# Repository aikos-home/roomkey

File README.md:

# RoomKey

**A key for every room: a small touch screen on two mechanical keyboard switches, in a 64 × 64 mm
housing that plugs into a wall socket. Doorbell, intercom, alarm and lights, one press away.
Built on ESP32-C6, ESPHome and Home Assistant.**

[Deutsch](README.de.md)

> Status: pre-alpha prototype. The firmware runs on the touch board on the desk; the microphone is
> verified on hardware. The housing v0.4 and kit v0.12 are designed in CAD, not printed yet; printed and
> assembled so far are the front stack and chassis of kit v0.10. The hub PCB is designed, not manufactured.
> State of this page: 31 October 2026.

<p align="center">
  
  <br><em>Target design — an AI-generated concept render (Google Gemini), not a photo of a built device.</em>
</p>

<p align="center">
  
  <br><em>The current design in FreeCAD: housing v0.4 in a SCHUKO socket. Build files in <a href="hardware/">hardware/</a>.</em>
</p>

## What it is

- **Plugs into a wall socket.** It runs on 5 V from an unmodified, certified USB charger inside
  the housing: no mains wiring, no electrician. The room's normal light switch stays where it is.
- **A key with a screen.** A 1.47″ touch display on top of a mechanical keyboard switch.
  **Press** does the obvious thing, **hold** does the deliberate thing, and the screen always
  says which is which. Tap and swipe for the rest.
- **The doorbell in every bedroom.** It rings, shows who is calling, and you answer with the
  key: hold to talk, release to listen.
- **The alarm, where you are.** Armed at night? Hold the key for 1.5 s to disarm — Home
  Assistant decides whether that room is allowed to.
- **Local and standard.** ESPHome native API: Home Assistant discovers it with ordinary
  entities, events and actions. No cloud, no custom integration.

It is the in-house counterpart of [Klingelbox](https://github.com/aikos-home/intercom), the
open-hardware door intercom.

## Status

| Area | State |
|---|---|
| UI + interaction state machine (lights, alarm, doorbell, call, menu, info) | ✅ done — runs on the board, verified in simulator and on hardware (scripted tour) |
| Home Assistant contract (subscriptions, light.toggle, disarm script, events, actions) | ✅ **11/11 against a real Home Assistant** (2026.9 dev instance, `tools/ha_contract_test.py`): lights toggle, disarm via HA policy (NIGHT allowed, AWAY refused), ring → answer / talk / hang-up events; also 11/11 against the fake HA incl. audio (`tools/fake_home.py --test`) |
| Demo mode (everything works standalone, no HA needed) | ✅ on by default |
| Status LED (WS2812 on the PoC board; glow ring on the touch board) | ✅ implemented — colours per state, not visually checked |
| Microphone (INMP441) | ✅ **verified on hardware** — wired, recorded: 1 kHz test beep +30 dB, speech +18 dB over the room; 120 Hz high-pass removes knock/handling rumble. Test: `esphome/mic_test.yaml` + `tools/mic_check.py` |
| Intercom audio, voice v2 (shared `aikos_voice` block: RTP/L16 16 kHz, push-to-talk, call model) | ✅ **desk key on v2 since 02.10.**: aikos re-acceptance with the door 71/71; simulator on the same block (`tools/voice_host_check.py`). The key's own audio path (`roomkey.yaml`) stays as the fallback. Listening needs the speaker (WIP, below) |
| Speaker + ringtone (MAX98357A + Waveshare 2030 cavity speaker 8 Ω 2 W) | 🟡 **WIP / opt-in** — compiles, commented out; parts ordered |
| Touch variant of the board (tap / swipe) | 🟡 **WIP** — required by the target design; arrived 02.10.: display, tap and swipe work on the board (`esphome/roomkey_touch.yaml`); chat swipe in a real call, mic, amp and glow ring on it still untested |
| Intercom security | ✅ incoming audio accepted only during an active call; everything else is dropped unheard |
| Door station side | ⬜ other milestone — spec in [docs/intercom-protocol.md](docs/intercom-protocol.md) |
| Optional sensors: SHT31-D climate, LD2410C mmWave presence | 🟡 bought; climate on the shared I²C bus (no extra pins), radar on UART; both placed in the housing in CAD. Light sensor (VEML6030) only in the PCB build (decided 31.10.) |
| Housing (plug-in, 64 × 64) and kit, two electronics builds (hub PCB / self-wired) | 🟡 designed in CAD, 0 collisions ([hardware/](hardware/)); not printed in this revision. The visible front is to be cast in resin; hub PCB rev D for this housing designed (DRC 0), not ordered |

## Inputs

| Screen | Tap | Swipe ↑ | Swipe ↓ | Key press | Key hold |
|---|---|---|---|---|---|
| Home | wakes, shows a hint — never an action | menu | — | all lights | menu · **disarm** when armed |
| Ringing | answer | — | silence this room | answer (on key-down) | answer + talk |
| Call | hold the disc = talk | — | hang up | hang up | push-to-talk |
| Menu | select | — | close | next | select |
| Alarm | — | — | — | hint | **disarm** (1.5 s) |

* A tap never switches anything on the home screen: fingers brush the screen whenever they
  press the key.
* A mechanical press always starts as a touch; key-down cancels that touch, so one press never
  fires twice.
* The key works on a dark screen — slap it in the dark to switch the lights.

## Hardware

The desk prototype runs on a **Waveshare ESP32-C6-LCD-1.47** (no touch). The target is the
**ESP32-C6-Touch-LCD-1.47** — same chip, touch layer, different size and pinout; the firmware
switches with one line.

### Board comparison (Waveshare drawings)

| | ESP32-C6-LCD-1.47 (PoC, non-touch) | ESP32-C6-Touch-LCD-1.47 |
|---|---|---|
| Outline | 36.4 × 20.3 mm bare PCB | 44.5 × 24.6 mm in black frame, 10.6 mm thick |
| Header | 2 × 9, one GND | 2 × 11, two GND, VBUS, VBAT |
| Mic SCK/WS/SD, L/R | IO18/IO19/IO23, L/R→IO0 | IO7/IO8/IO17, L/R→GND or IO3 |
| Amp BCLK/LRC/DIN, power | IO18/IO19/IO20, 5V | IO7/IO8/IO16, VBUS |
| Key | **IO1** + **IO2** (or the BOOT button) | BOOT + GND |

Firmware: swap the `board:` line in `roomkey.yaml`. The keycap is **not** interchangeable.

### Wiring (desk prototype: ESP32-C6-LCD-1.47)

| Part | Pins |
|---|---|
| Mechanical key switch | **IO1** + **IO2** (IO2 is held LOW by the firmware, because the header's only GND feeds the mic; no soldering; the onboard BOOT button works as the key too) |
| INMP441 mic | VDD→**3V3**, GND→**GND**, L/R→**IO0** (held low by firmware — the header has only one GND), SCK→**IO18**, WS→**IO19**, SD→**IO23** |
| I²S amp (WIP, e.g. MAX98357A) | VIN→**5V**, GND, BCLK→**IO18**, LRC→**IO19**, DIN→**IO20** |

INMP441 is bottom-port: the hole in its PCB must face the room. Mic and amp share the I²S
clocks → half-duplex by design (= push-to-talk, no echo).

Speaker: Waveshare 2030 cavity speaker (8 Ω, 2 W, 20 × 30 × 5.5 mm). Standing on its edge it fits
behind a side wing of the 55 × 55 mm plate — see the [fit check](docs/fit-check-speaker.png).

The housing, both electronics builds, print files and the build guide are in [hardware/](hardware/).

## Quick start

```bash
cd esphome
esphome run roomkey_v2.yaml         # build + flash over USB (first time) or OTA (roomkey.yaml = own audio, the fallback)
```
1. **Wi-Fi** (nothing is hardcoded): open https://web.esphome.io in Chrome → *Connect* →
   pick the board → enter Wi-Fi. Or join the hotspot `RoomKey Office` (password: `ap_password`
   in `esphome/secrets.yaml`).
2. **Home Assistant** discovers it; add it with the `api_key` from `esphome/secrets.yaml`,
   then enable *Allow the device to perform Home Assistant actions*.
3. Copy [homeassistant/roomkey_package.yaml](homeassistant/roomkey_package.yaml) into your HA packages.
4. Turn off the key's **Demo mode** switch once the entities exist.

One file per room: copy `roomkey_v2.yaml`, change `node_name`, `room_name` and the entity ids.

## Home Assistant contract

| Direction | What |
|---|---|
| key subscribes | `light.all_lights`, `alarm_control_panel.house`, `binary_sensor.doorbell_button` |
| key calls | `light.toggle`, `script.roomkey_disarm {room, entity_id}` (policy lives in HA) |
| key fires | event `esphome.roomkey {room, node, type}` · type ∈ answer, dismiss, call_door, hangup, talk_start, talk_stop |
| key offers | `ring`, `ring_stop`, `call_state(state)`, `show_toast(message)`, `set_intercom_peer(peer_host, peer_port)`, `simulate_alarm/lights/key` |
| entities | Demo mode, Screen brightness, Input (event: press/hold/…), Screen, Test doorbell, Wi-Fi, IP, intercom counters |

**Security note:** a disarm button in every room is also a disarm button for an intruder.
The key never stores a code — it *asks* HA, and the shipped script only allows disarming
HOME/NIGHT modes and a running entry delay/alarm, never AWAY. Decide that policy consciously.

## Develop without hardware

```bash
cd esphome
esphome compile sim.yaml                                   # desktop simulator (SDL)
.esphome/build/roomkey-sim/.pioenvs/roomkey-sim/program     # SPACE = key, mouse = touch
esphome compile sim_tour.yaml && RK_TOUR=1 RK_TOUR_EXIT=1 RK_SHOTS=shots .esphome/build/roomkey-tour/.pioenvs/roomkey-tour/program  # screenshot every state, cut off from the house
esphome compile sim_v2_check.yaml && python3 ../tools/voice_host_check.py   # voice v2 on the simulator against a fake door
~/.local/share/uv/tools/esphome/bin/python ../tools/fake_home.py --host localhost --test   # HA + door contract test (its audio checks: own audio path)
~/.local/share/uv/tools/esphome/bin/python ../tools/fake_home.py --host aikos-roomkey-desk.local  # interactive fake HA
```
`tour_device.yaml` runs the same tour on the real board and logs frame timings.

## Repository

| Path | What |
|---|---|
| [`esphome/roomkey_v2.yaml`](esphome/roomkey_v2.yaml) | device entry, one per room (voice v2, `aikos_voice`) |
| [`docs/wiring-touch-board.md`](docs/wiring-touch-board.md) | **wiring of the RoomKey Touch prototype**: every wire from the board to mic, amp, sensors, keys, LEDs |
| [`esphome/roomkey.yaml`](esphome/roomkey.yaml) | the same with the key's own audio path (fallback) |
| [`esphome/packages/`](esphome/packages/) | board contracts (PoC, touch, simulator) and feature packages: core UI, HA contract, mic, intercom, speaker |
| [`esphome/src/roomkey_ui.h`](esphome/src/roomkey_ui.h) | UI, input grammar and state machine (LVGL 9) |
| [`esphome/src/roomkey_audio.h`](esphome/src/roomkey_audio.h) | RTP/L16 audio link |
| [`homeassistant/`](homeassistant/) | HA package: disarm policy, ring-stop, door hooks |
| [`tools/fake_home.py`](tools/fake_home.py) | fake Home Assistant + door station: contract test and interactive console |
| [`tools/ha_contract_test.py`](tools/ha_contract_test.py) | the same contract against a real Home Assistant (with [`homeassistant/dev/roomkey.yaml`](homeassistant/dev/roomkey.yaml) stand-ins) |
| [`tools/mic_check.py`](tools/mic_check.py) | records the microphone and checks it hears a test sound |
| [`tools/privacy_scan.py`](tools/privacy_scan.py) | runs before every push |
| [`docs/north-star.md`](docs/north-star.md) | the target design and its decisions |
| [`docs/intercom-protocol.md`](docs/intercom-protocol.md) | audio format and call sequence |
| [`docs/handoff-doorbell-thread.md`](docs/handoff-doorbell-thread.md) | the interface agreed with Klingelbox |

## Performance notes (ESP32-C6, no PSRAM)

RAM 36 % used. Measured on hardware: steady-state LVGL frames 30–80 ms, full view
switches ≈ 100 ms. Software shadows, transform-scaled press animations and a full-screen
alarm tint were replaced by outline halos, size animation and edge bars after the
first hardware run showed 140 ms frames.

## Next steps

1. Print and fit the housing v0.4 and kit v0.12; cast the visible front in resin. RoomKey is built as a
   plug-in device only (decided 31.10.): a 64 × 64 housing on a SCHUKO socket, 5 V safety extra-low voltage
   from an unmodified, certified USB charger inside it; no mains wiring. Details and open questions:
   [hardware/docs/plug-in-housing.md](hardware/docs/plug-in-housing.md).
2. Hub PCB rev D for this housing is designed: [hardware/pcb/roomkey-hub/](hardware/pcb/roomkey-hub/) (DRC 0, nothing
   ordered). Next: decide whether to order it.
3. Speaker, amp and glow ring on the touch board.
4. Later (decided 30.09.): voice identification, so the family members are told apart even when they
   don't say their name. Local speaker embeddings on the transcriber host, enrolled with ~1 min of speech
   per person through the key's mic. Display only, never for opening doors or disarming. Needs everyone's
   consent; visitors' voices are only compared, never stored.
5. Later (nice to have): translate a resident's answer into the visitor's language on the door screen
   (today every transcript is shown in German; the original words stay in `text_original`).

## Privacy

- The microphone only runs while you hold the key during a call, or while the *Room info*
  screen shows its live level meter. Nothing is recorded or sent otherwise.
- Exceptions you switch on yourself: "Transcriber address" sends a copy of what you say during a call
  (push-to-talk only) to your local transcriber; the WIP test switch "TEST record after ring" records the
  room after every ring and says so on screen. Both are off by default.
- Incoming audio is only accepted during an active call. Keep RoomKeys in the IoT VLAN, like the
  door devices.

## Safety

- RoomKey takes 5 V only (SELV). In the housing, 230 V stays inside an unmodified, certified USB charger;
  never open or modify it, and wire nothing of the RoomKey to mains.
- On the bench, power it from a lab supply (5.0 V, current-limited) or USB.

## Licences

- Code (firmware, scripts): [MIT](LICENSE), except the AXS5106L touch driver in
  `esphome/components/axs5106l/`, which keeps its own [MIT licence](LICENSES/MIT-axs5106l-Olivier-Latignies.txt)
- Icon font (Material Design Icons): [Pictogrammers Free License](LICENSES/MDI-Pictogrammers-Free-License.txt)
- Hardware designs (CAD scripts, STL, STEP): [CERN-OHL-P-2.0](LICENSES/CERN-OHL-P-2.0.txt)
- Documentation and images: [CC BY 4.0](LICENSES/CC-BY-4.0.txt)

Designed and written with [Claude Code](https://claude.com/claude-code).

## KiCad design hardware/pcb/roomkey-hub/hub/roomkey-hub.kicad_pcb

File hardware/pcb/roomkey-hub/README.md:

# RoomKey hub PCB set

Three small boards replace the kit's loose breakouts and hand wiring. **Status 2026-10-31: hub rev D routed (rev B after an
independent review; rev C: the 5 V input J1 as a JST PH plug; rev D: fitted to the 64 × 64 plug-in housing — square
outline, radar in the hub plane, J1 side entry), DRC 0/0/0, order files ready, nothing ordered (pre-alpha); the small
boards are schematics only.** Decisions: owner, 2026-10-08 and 2026-10-31.

| Board | Folder | Where it sits | What it carries |
|---|---|---|---|
| **Hub** | `hub/` | static, directly behind the switch plate; the two MX switches plug into it | 5 V input + protection, MX hot-swap sockets, amplifier, I²S mic, 3.3 V regulator, LED data buffer; plugs for radar, speaker and sensor tail; a side-entry JST PH plug for the 5 V lead (J1); solder holes for the key wires and the glow LEDs |
| **Sensor tail** | `sht-tail/` | the frame's bottom border, in room air and light | SHT40 temperature/humidity + VEML6030 light sensor on a 4-pin Qwiic cable |
| **Pogo adapter** | `pogo/` | on the touch board, moves with the key | 15 spring pins on the bare H1 pads → 16-pin FFC to the hub (later; the first order is wired) |
| **Glow LEDs** | — | behind the 4 corners of the clear collar, facing forward | 4 × WS2812B-Mini 3535, hand-wired (owner ordered 50 loose, 2026-10-03), chain from J8. No LED board (owner, 2026-10-12, see Open points) |

**One RoomKey (owner, 2026-10-08):** no variants. The only push-buttons are the two MX switches under the one rigid
key (IO9 top, IO6 bottom; the firmware ORs them). The plate is fixed. So the hub has **no plate input and no I/O
expander**: it uses exactly the kit's ESP pins, and the firmware needs no change for it.

**Power:** only 5 V SELV reaches RoomKey: RoomKey is built as a plug-in device only (owner, 2026-10-31). A
certified, unmodified USB charger (revolt PX-8884, 5 V 2.1 A) sits behind it in the housing; a short lead from a
solder-type USB-A plug in the charger plugs into J1 (JST PH 2-pin, side entry). **No board here ever carries 230 V.**

**Why several KiCad projects:** KiCad has one PCB per project. The one thing they share, the key-wire / FFC order between
hub and pogo adapter, is defined once in `gen_schematics.py` (`FFC_PINS`) and written into both schematics.

## Files

- `gen_schematics.py` — the source of the schematics: parts, values, part numbers (MPN, LCSC), nets. It writes the
  `.kicad_sch` files and `lib/roomkey.kicad_sym`, and checks that no texts overlap, no two nets touch and every named
  net reaches at least two pins.
- `hub/`, `sht-tail/`, `pogo/` — KiCad 10 projects. `hub/roomkey-hub.kicad_pcb` is the routed board.
- `lib/roomkey.kicad_sym`, `lib/roomkey.pretty` — symbols and footprints KiCad does not ship (TPS25200, VEML6030,
  MAX98357A with its exposed pad as a passive pin; Mill-Max 0900 spring pin; Kailh MX hot-swap socket).
- `output/*.pdf` schematics, `output/*-bom.csv` grouped BOMs (MPN + maker), `output/jlcpcb/` the order files,
  `output/roomkey-hub.step` for the kit CAD (exported with `--subst-models --no-dnp`: bare solder holes carry no model), `output/roomkey-hub_overview_de.png` (what is what, German),
  `output/roomkey-hub_soldering-map.png` (where each wire goes).

Scripts (run in this order with KiCad's Python, `"C:/Program Files/KiCad/10.0/bin/python.exe"`):
1. `gen_schematics.py` — schematics + project library; then `kicad-cli sch erc` on each.
2. `gen_layout_hub.py` — outline from the kit CAD and placement (all parts on the back).
3. `route_hub.py` — re-runs 2, GND/+5V fan-out vias, Freerouting (Java 25 + freerouting-2.5.0.jar in `~/tools` or
   `$ROOMKEY_TOOLS`, downloaded with the owner's OK; it opens a window while it works), keeps the best round, GND pours.
   Freerouting is randomised, so the routed `.kicad_pcb` is the artifact.
4. `complete_route.py` — rip-up-and-reroute where it helps, then closes leftovers on F.Cu/B.Cu by grid search.
5. `export_jlc.py` — Gerbers + drill zip, BOM and CPL in JLCPCB's format into `output/jlcpcb/`.
6. `overview_map.py`, `soldering_map.py` — the two pictures. `add_wire_hole.py` — only if a key wire ever has to leave
   the 2 × 8 field: a single hole on its net's routed copper.

## What the hub does

1. **Power.** JST PH plug J1 for the 5 V lead from the USB charger (side entry, through-hole, 2 A; pin 2 = +5 V; the
   lead is AWG 24 at most, PH crimps take no thicker wire — 1.5 A over 10 cm drops ≈ 13 mV) → bidirectional TVS (ESD/surge) → P-FET Q1 (reverse polarity)
   → eFuse TPS25200 (current limit 1.5 A typ via R2 = 64.9 k; output clamp 5.25–5.55 V for 5.4–7.6 V in, output off
   above 6.8 V, so a 12 V supply by mistake is harmless; IN rated to 20 V; soft start; thermal cut-out) → **+5V node**
   (TVS, 100 µF) for amplifier, radar and LED ring. +5V → Schottky D4 → **VBUS_KEY** → the touch board's VBUS pad.
   D4 keeps the touch board's USB power out of the hub. The 3.3 V regulator (mic, key pull-ups, sensor tail) is fed from
   either side through the dual diode D5, so I²C and the IO8 pull-up are live whenever the key has power.
2. **Audio.** MAX98357A as on the kit's breakout (1 MΩ on SD_MODE = mono mix, gain 9 dB; standby whenever BCLK stops)
   + an ICS-43434 I²S MEMS mic on the same bus (half duplex, as today). Bottom port, through a 0.5 mm hole in the board
   at the sound tube's axis (−20.16, 9.6). IO8 (I²S WS) has its 10 k pull-up for the strapping.
3. **I²C** only goes on to the sensor tail plug J9 (Qwiic order GND, 3V3, SDA, SCL). The touch board already pulls the
   bus up (10 k); the hub's pull-ups R11/R12 are not fitted. Addresses: VEML6030 0x10, SHT40 0x44 (or the kit's SHT31
   0x44), touch 0x63, IMU 0x6B — no clashes.
4. **Switches and plugs.** The MX switches plug straight into Kailh hot-swap sockets (10 k pull-ups to 3.3 V). Radar
   on a cable (JST SH 5-pin in the module's silkscreen order TX, RX, OUT, GND, VCC; OUT is not used — presence comes over
   the UART — but keeps the cable 1:1). Glow LEDs through a 3.3 → 5 V buffer + 330 Ω, with 100 nF + 10 µF for the chain start, into three solder holes J8
   near the bottom-right corner (see layout). Speaker: 2-pin 1.25 mm.

## First order (owner, 2026-10-08): 7 hubs at JLCPCB, key wired

- **JLCPCB** (PCBWay's per-design setup made a first run ≈ €650). Order 10 bare hubs, **7 assembled**.
- **Standard PCBA, not Economic:** the ICS-43434 mic (C5656610) is "Standard Only" at JLCPCB (leadless, X-ray). All
  other parts allow both. Rough total ≈ €170–240 incl. shipping and VAT (Standard adds ≈ €25 of setup and stencil);
  the exact figure comes from JLCPCB's quote.
- **Only the hub** in this order. The kit's SHT31-D breakout plugs into J9 with a ready-made JST SH cable (pigtail
  soldered to the breakout); the radar with a ready-made JST SH 5-pin ↔ 2.54 mm Dupont cable (order kept 1:1). The
  glow LEDs are hand-wired as in the kit, their chain start into J8. Sensor tail and pogo link later.
- **Key wired, as in the kit:** all key wires go into one 2 × 8 field of 1.27 mm solder holes (J4, same order as a later
  FFC). J4 is not assembled. J1 is a JST PH plug that JLCPCB solders (through-hole): the 5 V lead plugs in.

**Ordering** (the owner orders; nothing is uploaded from here):
1. jlcpcb.com → upload `output/jlcpcb/roomkey-hub_gerbers.zip` (4 layers, 1.6 mm), quantity 10, ENIG or HASL lead-free.
2. PCB Assembly on → **Standard** → **assembly side: bottom** → 7 boards → "Confirm parts placement": yes. If JLCPCB
   wants edge rails or tooling holes, accept them on the rails (not in the board).
3. Upload `roomkey-hub_bom.csv` and `roomkey-hub_cpl.csv`.
4. **Placement preview — send screenshots before paying.** Every part must sit on its pads, and every polarised part
   with pin 1 on its pin-1 pad: U1, U2, U3, U4, U7, Q1, D2, D3, D4, D5, J1, J2, J5, J9, SW1, SW2. Rotate in the preview
   where needed. The CPL already mirrors bottom-side rotations (`180 − rot`) and places the MX sockets by their body
   centre, but package zero orientations differ between KiCad's and JLCPCB's libraries, so this check is mandatory.

**Independent review, 2026-10-08** (read-only agent, every IC pin by pin against the data sheet, every LCSC number
against its footprint, strapping, JLCPCB rules): **no wrong pin, part or value found.** Fixed after it: Standard PCBA
for the mic; CPL bottom rotations and MX socket positions; BOM without "C11-C13" ranges; J4 moved clear of MX1's
housing (solder fillets under a switch that sits flat on the board). Notes kept:
- With J1 powered, the touch board's USB-C VBUS carries ≈ 4.7 V (the board has no diode there). To flash over USB,
  unplug the supply; never plug into a switched-off PC while J1 has power.
- On the touch board, the IMU's interrupt outputs share IO5 (radar RX) and IO6 (bottom key) — as in the kit. The
  firmware must keep the QMI8658 interrupts disabled.

## Hub layout

- **Where:** directly behind the switch plate, front face at d 20.3 (MX housing bottom); 1.6 mm, **4 layers**: F.Cu
  signals, In1 GND plane, In2 +5V plane, B.Cu parts + signals. All parts on the back (single-sided assembly). The
  front is bare except the switch holes.
- **Outline, rev D** (kit CAD, `hardware/cad/insert_params.py`, branch `kit-pcb`, plug-in housing v0.4, 64 × 64):
  square ±28.0 (0.45 to the lid's side walls) minus
  - the housing's corner columns: a circle r 3.9 round (±26.8, ±26.8) and everything beyond it toward the corner
    (column r 3.2 + 0.5 air + 0.2 for the router's tolerance);
  - the speaker + cradle (x ≥ 14.3 for |y| ≤ 17.2);
  - the radar window (x ≤ −7.86, y −18.4…6.2, open to the left edge): the LD2410C now sits **in** the hub plane, its
    antenna face flush with the board's front, in a printed cage;
  - a bottom notch (x −4.3…9.84, up to y −25.87) that the humidity sensor and its lead pass.

  A slot 12.8 × 2.6 at y 1.5 takes the key wires. M2 screws at (−13.2, 20), (13.2, 20), (10.5, −7.9); a plain support
  post at (13.2, 4). The window's inner corners come out rounded (r ≈ 0.5, the router bit).
- **Fixed by the CAD:** mic port at (−20.16, 9.6); J4 centred at (0, 6.35), both rows below MX1's housing (y < 8.0) and
  inside the wire loop's zone (x ±7, y 0.2–11; only flat passives ≤ 1.3 mm under the loop); radar plug J5 at
  (−13.5, 10.5), body y 7…14, its wires soldered to the radar's header pins (cut to 2 mm, x −22.7); speaker plug J2
  at its rev C place (11.5, 12.5); 5 V plug J1 (side entry): pins at x 12.75 (pin 2 = +5 V at y −1.5, pin 1 = GND
  at y −3.5), body x 6.5…14.1, y −5.45…0.45, 0.45 mm above the head of H3's M2 screw and 0.5 mm left of the
  speaker foam. Its mouth faces the axis: the lead comes from the USB plug's solder cups (x −3.3 / 3.7, y −5.35)
  through a lane kept free of parts (x −4.5…6.5, y −6.0…−0.5). The mouth faces −x and not down because the plug would
  have to slide in over H3's screw head. Through-hole pins stay outside both MX housings (`gen_layout_hub.py` checks
  that no through-hole joint lies under a 14 × 14 housing). **Clip J1's two pin tails on the front to ≤ 1.0 mm**
  (side cutter): wave-soldered tails can be longer, and the front is only 2.5 mm from the switch plate. The input
  protection (D1, Q1, U1 …) sits below J1's lane, between it and MX2's socket; glow LED holes J8 at x 15.3, y −19.2…−21.8 (just outside the collar seat wall / switch-plate ledge, so the wires
  enter straight): the LEDs sit in FRONT of the hub
  (d 12.6–15.4), so their wires come from the bottom-right LED (12.5, −22.47) through the switch-plate notch into the
  3.5 mm gap in front of the hub and into these holes (a plug on the back could not be reached; an SH plug on the
  front is 4.25 tall).
- **Rules:** tracks 0.15 / gaps 0.125 mm (JLCPCB 4-layer allows 0.09), supply and speaker 0.3, vias 0.6/0.3, copper
  ≥ 0.3 mm from the edge. `hub/roomkey-hub.kicad_dru` has one rule: J1's and H3's courtyards may overlap (the stock
  mounting-hole courtyard is bigger than the M2 head; J1's body stays 0.45 mm clear of it). DRC leaves two silkscreen
  warnings: J1's outline touches the slot's end, and the board house clips it there.

**Soldering the wires** — map: `output/roomkey-hub_soldering-map.png` (seen from the back, holes at their real
positions). Touch board pad (silkscreen name) → hub hole:

| Touch pad | Hub hole | | Touch pad | Hub hole |
|---|---|---|---|---|
| VBUS | J4-1 (J4-2 spare) | | SDA | J4-9 |
| GND (×3) | J4-3, J4-11, J4-14 | | SCL | J4-10 |
| 9 (key top) | J4-4 | | TXD | J4-12 |
| 6 (key bottom) | J4-5 | | 7 | J4-13 |
| 4 (LED data) | J4-6 | | 8 | J4-15 |
| 5 | J4-7 | | RXD | J4-16 |
| 3 | J4-8 | | 5 V lead + / − | J1 plug pin 2 / pin 1 (plugs in, no soldering) |
| glow LED chain: data (DIN of the BR LED) | J8-3 | | glow LED chain: +5 V / GND | J8-2 / J8-1 |

The square hole is J4-1. Never connect the touch board's 3V3, VBAT, RST, IO1, IO2, IO12, IO13 pads.

The 5 V lead: solder it to the USB-A plug (VBUS = +5 V, GND) and crimp or buy it with a JST PHR-2 housing so that
+5 V lands on J1's pin 2 — the contact toward the board's top edge (toward the amplifier) when the hub is upright.
The plug only fits one way round; check the wire colours against the soldering map before the first power-up.

## Open points

Only the owner can check (part in hand):
- [x] LD2410C pin order (J5): TX, RX, OUT, GND, VCC — owner's photo, 2026-10-08.
- [ ] Speaker plug (J2): 2-pin 1.25 mm ("PH1.25 2P", owner); the CJT A1251WV-S-2P is a PicoBlade-size part — check
      the fit when the boards arrive.

Design / later boards:
- [ ] Sensor tail layout, after hub rev D. The CAD's frame (2026-10-31): flat in the lid G2's bottom wall, parts facing
      down (−y) to the vents; ≤ 13.4 (x) × 10.5 (depth) × 2.6 overall, board x −3.9…9.44, d 9.6…20.1, parts only in
      x −2.9…8.44 (the 1 mm ends rest on G2's wall); SHT40 over the vents at x 3.3, VEML6030 over the light window at
      x −1.0 (both d 13.35); solder pads for the 4 wires at the back edge (d ≈ 18.5), on the top (+y).
- [x] Glow LEDs stay **hand-wired, no LED board** (owner, 2026-10-12). A closed ring does not fit (CAD 2026-10-09);
      4 corner boards were laid out and dropped: they don't save any soldering (4 wires per LED either way) and
      the 0.6 mm board forces JLCPCB's Standard assembly (≈ €45–60). Chain BR → TR → TL → BL from J8 (CAD thread,
      both builds). Don't resurface.
- [ ] Pogo adapter + FFC (replaces the key wires in a later order).
- [ ] Firmware (later): VEML6030 via the `veml7700` platform and SHT4x once the sensor tail exists; nothing else changes.

Parts considered and not used: PTC fuse (the eFuse does more), SPH0645 mic (non-standard I²S → firmware change),
OPT3001 (0x44 = SHT clash), TCA9534 I/O expander and plate input (no plate button, owner 2026-10-08).

## Sources

- Pins: `docs/wiring-touch-board.md`, `esphome/packages/board_c6_touch_lcd_147.yaml`, Waveshare
  ESP32-C6-Touch-LCD-1.47 schematic
- TPS25200 (TI SLVSCJ0F: pinout, ILIM, EN ≥ 300 k, OVP 7.4.3/7.4.4), TPS7A20, MAX98357A (SD_MODE table, standby),
  ICS-43434 (TDK DS-000069), SN74AHCT1G125, AO3401A, PMEG3020EH, BAT54C — maker data sheets
- JLCPCB part pages (PCBA type per part), JLCPCB assembly price article, KiBot notes on JLCPCB bottom rotation
- LD2410C: Hi-Link serial protocol document, table 1

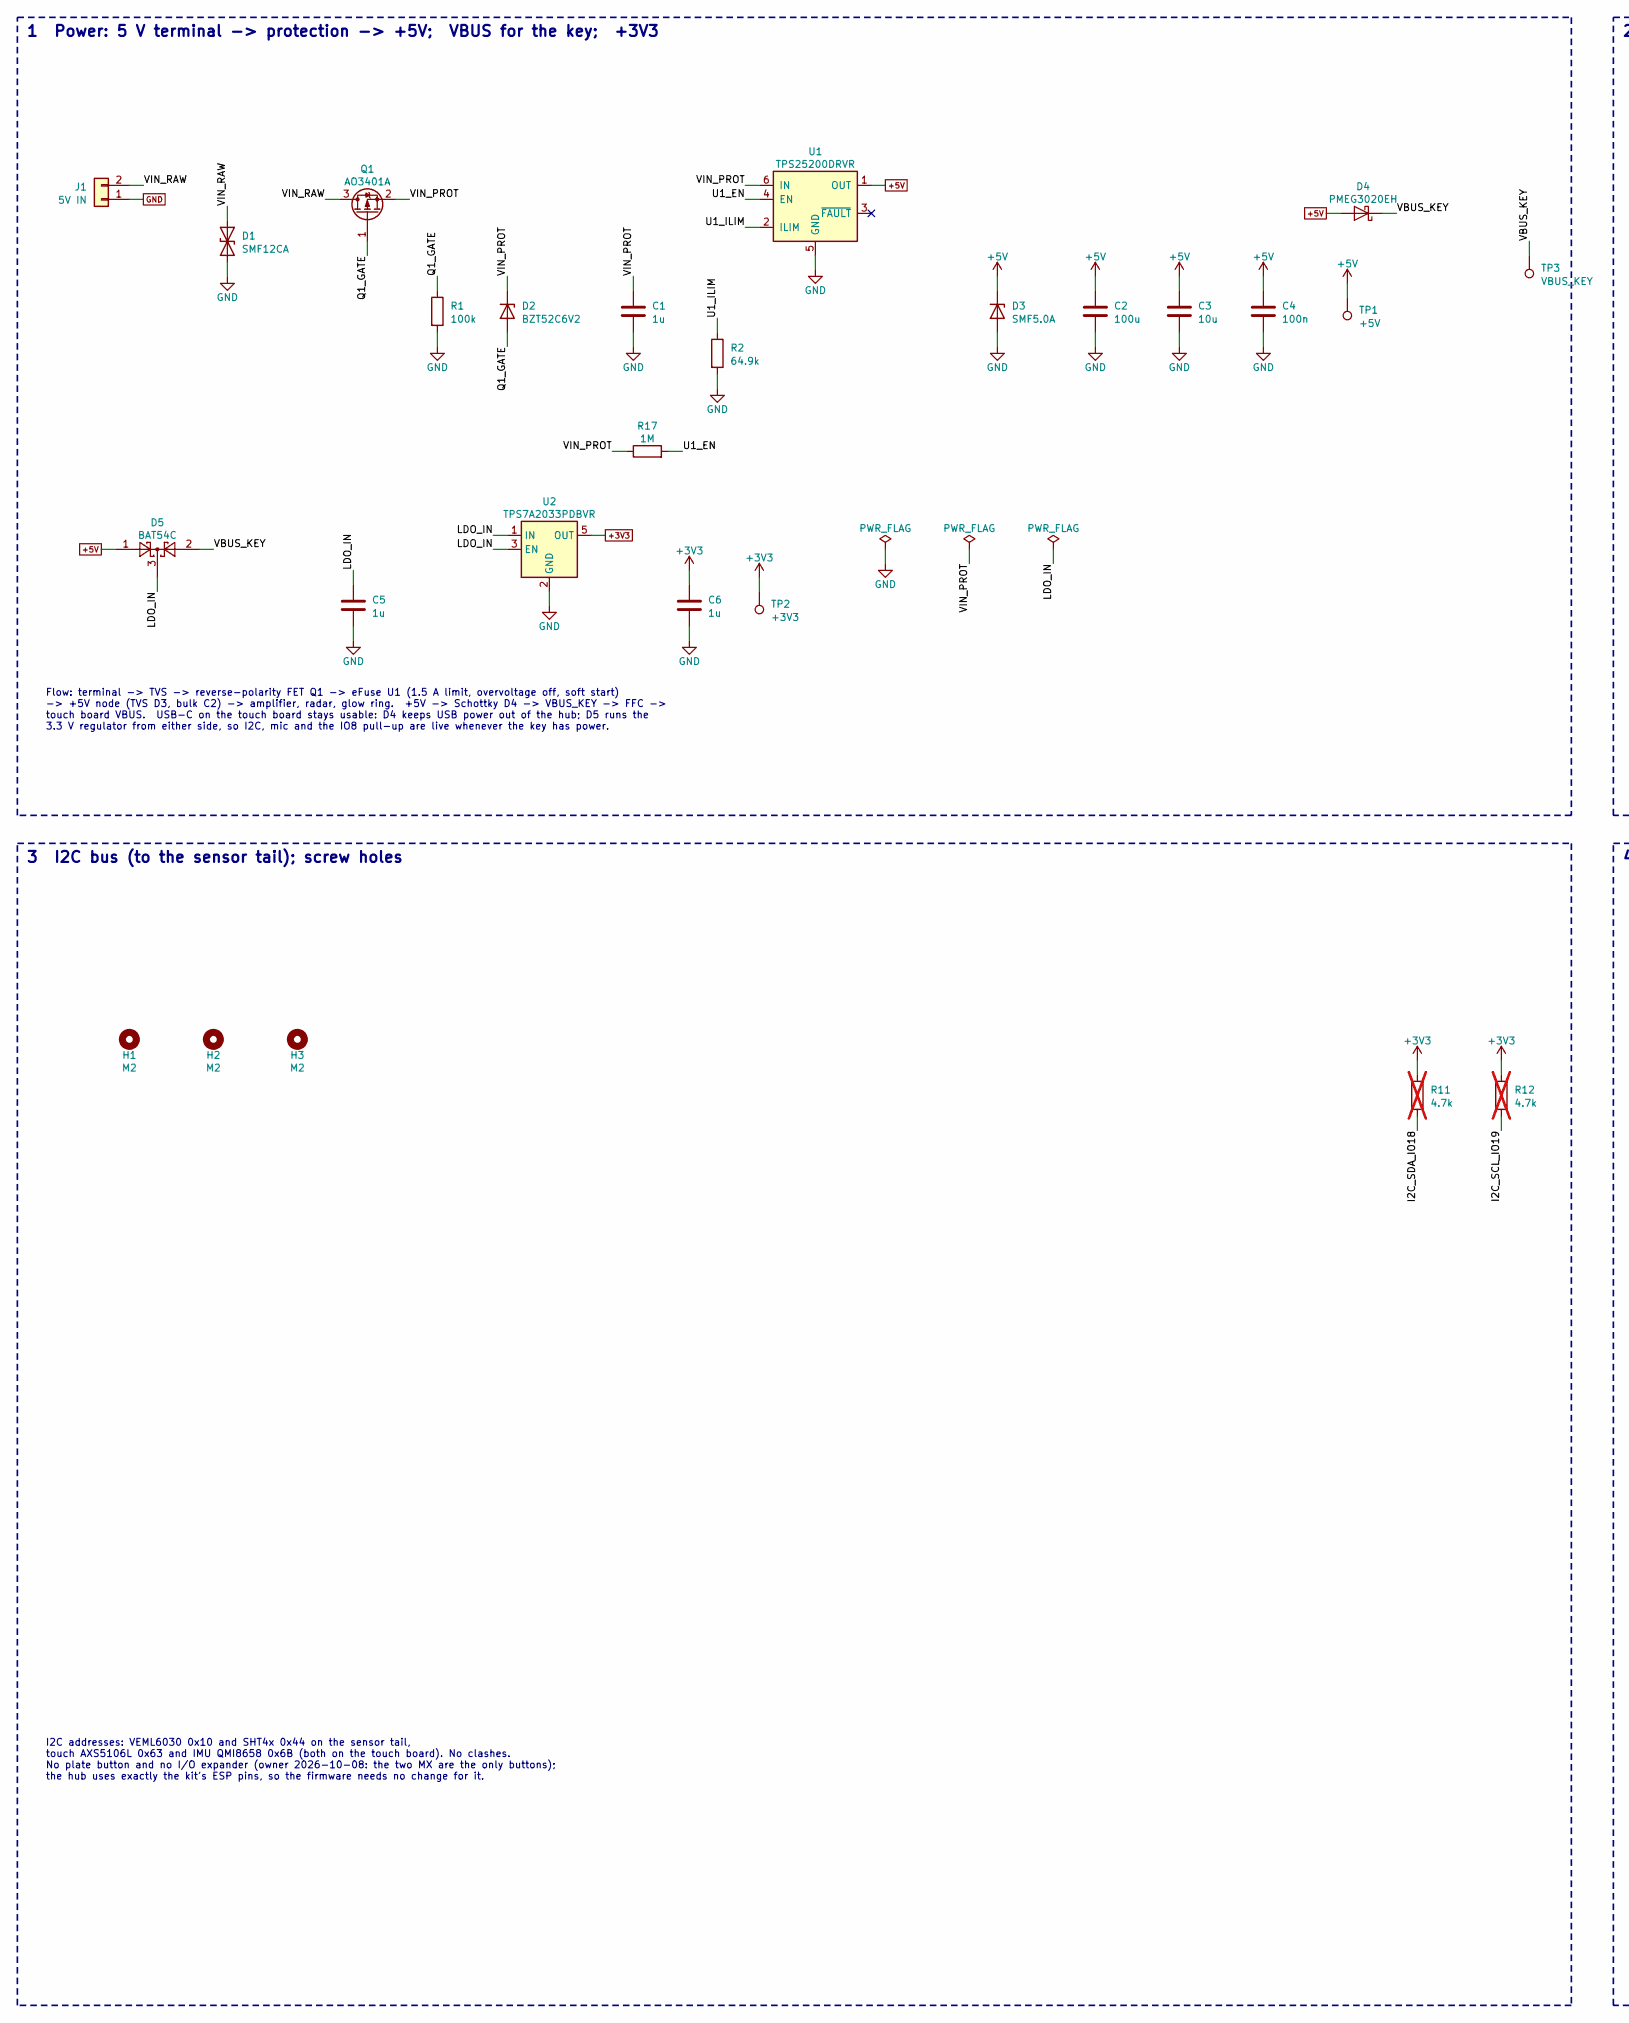
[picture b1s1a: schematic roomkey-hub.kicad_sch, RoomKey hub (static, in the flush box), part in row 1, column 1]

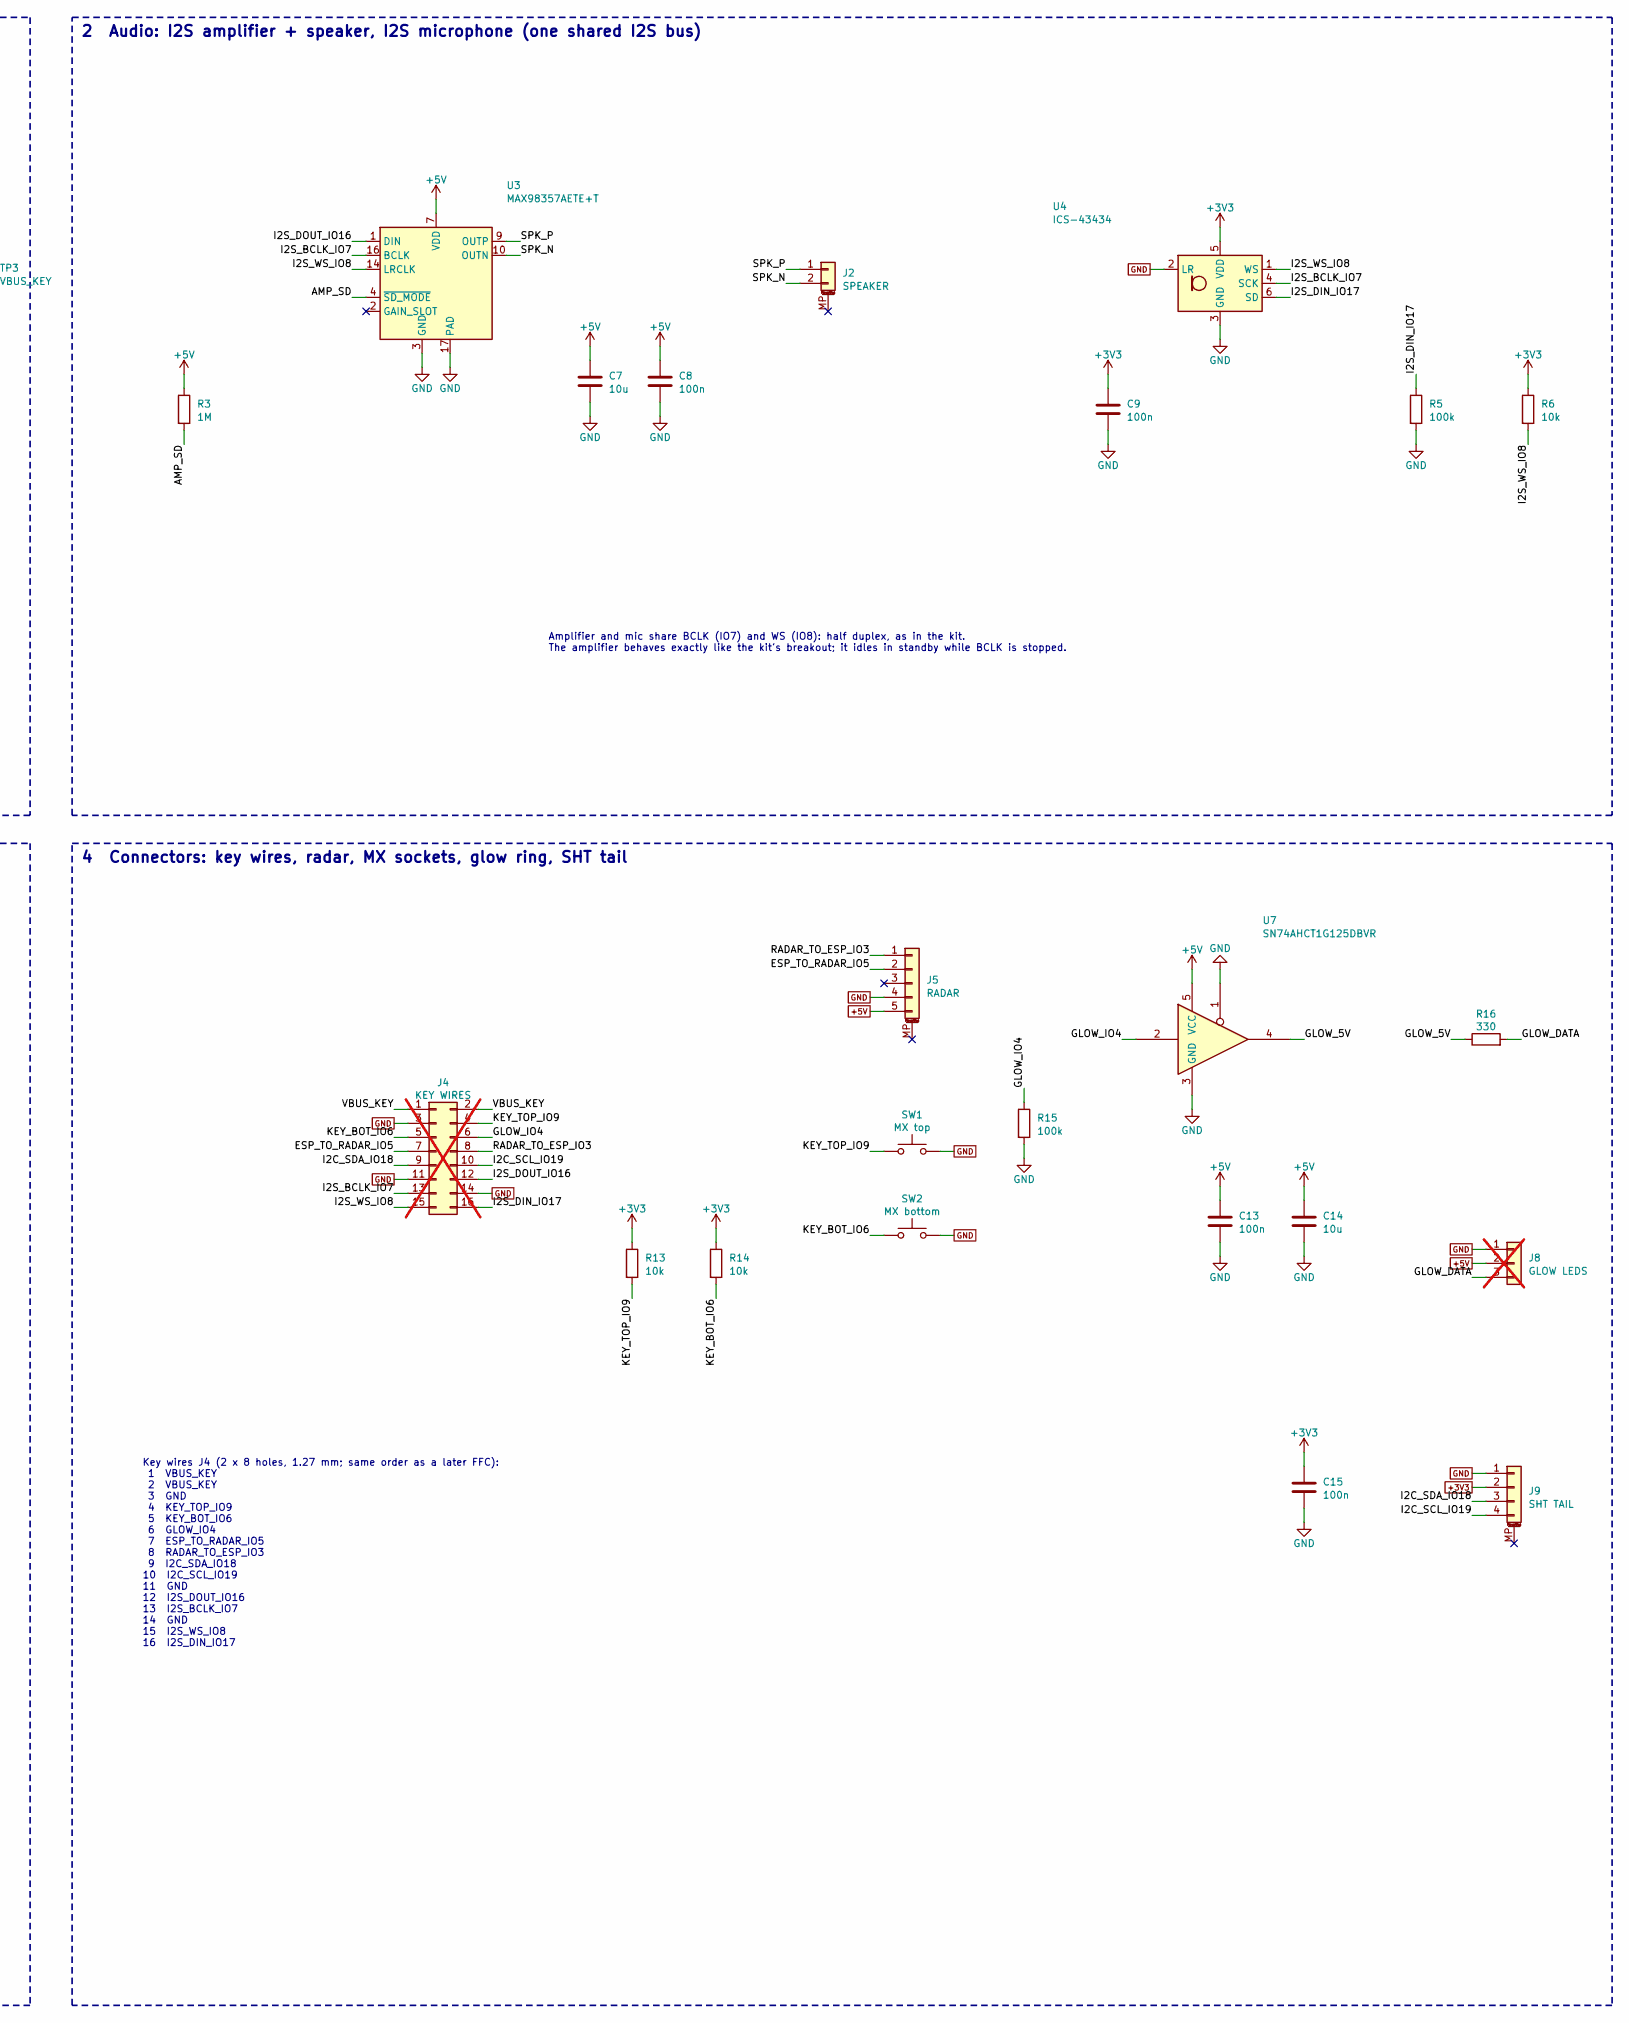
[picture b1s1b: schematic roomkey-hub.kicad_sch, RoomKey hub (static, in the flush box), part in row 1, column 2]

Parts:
C1, C5, C6: 1u; C_0603_1608Metric; MPN CL10A105KB8NNNC; LCSC C15849
C2: 100u; C_1206_3216Metric; MPN CL31A107MQHNNNE; LCSC C15008
C3, C7, C14: 10u; C_0805_2012Metric; MPN CL21A106KAYNNNE; LCSC C15850
C4, C8, C9, C13, C15: 100n; C_0402_1005Metric; MPN CL05B104KO5NNNC; LCSC C1525
D1: SMF12CA; D_SOD-123F; MPN SMF12CA; LCSC C123801
D2: BZT52C6V2; D_SOD-123; MPN LBZT52C6V2T1G; LCSC C27091
D3: SMF5.0A; D_SOD-123F; MPN SMF5.0A; LCSC C193402
D4: PMEG3020EH; D_SOD-123F; MPN PMEG3020EH; LCSC C19268151
D5: BAT54C; SOT-23; MPN BAT54C; LCSC C2135
H1, H2, H3: M2; MountingHole_2.2mm_M2
J1: 5V IN; JST_PH_S2B-PH-K_1x02_P2.00mm_Horizontal; MPN S2B-PH-K-S(LF)(SN); LCSC C173752
J2: SPEAKER; Molex_PicoBlade_53398-0271_1x02-1MP_P1.25mm_Vertical; MPN A1251WV-S-2P; LCSC C225104
J4: KEY WIRES; PinHeader_2x08_P1.27mm_Vertical; not fitted
J5: RADAR; JST_SH_BM05B-SRSS-TB_1x05-1MP_P1.00mm_Vertical; MPN BM05B-SRSS-TB(LF)(SN); LCSC C160391
J8: GLOW LEDS; PinHeader_1x03_P1.27mm_Vertical; not fitted
J9: SHT TAIL; JST_SH_BM04B-SRSS-TB_1x04-1MP_P1.00mm_Vertical; MPN BM04B-SRSS-TB(LF)(SN); LCSC C160390
Q1: AO3401A; SOT-23; MPN AO3401A; LCSC C15127
R1, R5, R15: 100k; R_0402_1005Metric; MPN 0402WGF1003TCE; LCSC C25741
R2: 64.9k; R_0402_1005Metric; MPN 0402WGF6492TCE; LCSC C26984
R3, R17: 1M; R_0402_1005Metric; MPN 0402WGF1004TCE; LCSC C26083
R6, R13, R14: 10k; R_0402_1005Metric; MPN 0402WGF1002TCE; LCSC C25744
R11, R12: 4.7k; R_0402_1005Metric; MPN 0402WGF4701TCE; LCSC C25900; not fitted
R16: 330; R_0402_1005Metric; MPN 0402WGF3300TCE; LCSC C25104
SW1: MX top; SW_MX_Hotswap_Kailh_1.00u; MPN CPG151101S11-2; LCSC C49352235
SW2: MX bottom; SW_MX_Hotswap_Kailh_1.00u; MPN CPG151101S11-2; LCSC C49352235
TP1: +5V; TestPoint_Pad_D1.0mm
TP2: +3V3; TestPoint_Pad_D1.0mm
TP3: VBUS_KEY; TestPoint_Pad_D1.0mm
U1: TPS25200DRVR; WSON-6-1EP_2x2mm_P0.65mm_EP1x1.6mm; MPN TPS25200DRVR; LCSC C128401
U2: TPS7A2033PDBVR; SOT-23-5; MPN TPS7A2033PDBVR; LCSC C2862740
U3: MAX98357AETE+T; TQFN-16-1EP_3x3mm_P0.5mm_EP1.23x1.23mm; MPN MAX98357AETE+T; LCSC C910544
U4: ICS-43434; InvenSense_ICS-43434-6_3.5x2.65mm; MPN ICS-43434; LCSC C5656610
U7: SN74AHCT1G125DBVR; SOT-23-5; MPN SN74AHCT1G125DBVR; LCSC C7484

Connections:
+3V3: C6.1, C9.1, C15.1, J9.2, R6.1, R11.1, R12.1, R13.1, R14.1, TP2.1, U2.5 (OUT), U4.5 (VDD)
+5V: C2.1, C3.1, C4.1, C7.1, C8.1, C13.1, C14.1, D3.1 (K), D4.2 (A), D5.1, J5.5, J8.2, R3.1, TP1.1, U1.1 (OUT), U3.7 (VDD), U3.8 (VDD), U7.5 (VCC)
/AMP_SD: R3.2, U3.4 (~SD_MODE)
/ESP_TO_RADAR_IO5: J4.7, J5.2
/GLOW_5V: R16.1, U7.4
/GLOW_DATA: J8.3, R16.2
/GLOW_IO4: J4.6, R15.1, U7.2
/I2C_SCL_IO19: J4.10, J9.4, R12.2
/I2C_SDA_IO18: J4.9, J9.3, R11.2
/I2S_BCLK_IO7: J4.13, U3.16 (BCLK), U4.4 (SCK)
/I2S_DIN_IO17: J4.16, R5.1, U4.6 (SD)
/I2S_DOUT_IO16: J4.12, U3.1 (DIN)
/I2S_WS_IO8: J4.15, R6.2, U3.14 (LRCLK), U4.1 (WS)
/KEY_BOT_IO6: J4.5, R14.2, SW2.1
/KEY_TOP_IO9: J4.4, R13.2, SW1.1
/LDO_IN: C5.1, D5.3, U2.1 (IN), U2.3 (EN)
/Q1_GATE: D2.2 (A), Q1.1 (G), R1.1
/RADAR_TO_ESP_IO3: J4.8, J5.1
/SPK_N: J2.2, U3.10 (OUTN)
/SPK_P: J2.1, U3.9 (OUTP)
/U1_EN: R17.2, U1.4 (EN)
/U1_ILIM: R2.1, U1.2 (ILIM)
/VBUS_KEY: D4.1 (K), D5.2, J4.1, J4.2, TP3.1
/VIN_PROT: C1.1, D2.1 (K), Q1.2 (S), R17.1, U1.6 (IN)
/VIN_RAW: D1.1 (A1), J1.2, Q1.3 (D)
GND: C1.2, C2.2, C3.2, C4.2, C5.2, C6.2, C7.2, C8.2, C9.2, C13.2, C14.2, C15.2, D1.2 (A2), D3.2 (A), J1.1, J4.3, J4.11, J4.14, J5.4, J8.1, J9.1, R1.2, R2.2, R5.2, R15.2, SW1.2, SW2.2, U1.5 (GND), U1.7 (EP), U2.2 (GND), U3.3 (GND), U3.11 (GND), U3.15 (GND), U3.17 (PAD), U4.2 (LR), U4.3 (GND), U7.1, U7.3 (GND)

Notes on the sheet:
1 Power: 5 V terminal -> protection -> +5V; VBUS for the key; +3V3
Flow: terminal -> TVS -> reverse-polarity FET Q1 -> eFuse U1 (1.5 A limit, overvoltage off, soft start) -> +5V node (TVS D3, bulk C2) -> amplifier, radar, glow ring. +5V -> Schottky D4 -> VBUS_KEY -> FFC -> touch board VBUS. USB-C on the touch board stays usable: D4 keeps USB power out of the hub; 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
2 Audio: I2S amplifier + speaker, I2S microphone (one shared I2S bus)
Amplifier and mic share BCLK (IO7) and WS (IO8): half duplex, as in the kit. The amplifier behaves exactly like the kit's breakout; it idles in standby while BCLK is stopped.
3 I2C bus (to the sensor tail); screw holes
I2C addresses: VEML6030 0x10 and SHT4x 0x44 on the sensor tail, touch AXS5106L 0x63 and IMU QMI8658 0x6B (both on the touch board). No clashes. No plate button and no I/O expander (owner 2026-10-08: the two MX are the only buttons); the hub uses exactly the kit's ESP pins, so the firmware needs no 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
4 Connectors: key wires, radar, MX sockets, glow ring, SHT tail
Key wires J4 (2 x 8 holes, 1.27 mm; same order as a later FFC): 1 VBUS_KEY 2 VBUS_KEY 3 GND 4 KEY_TOP_IO9 5 KEY_BOT_IO6 6 GLOW_IO4 7 ESP_TO_RADAR_IO5 8 RADAR_TO_ESP_IO3 9 I2C_SDA_IO18 10 I2C_SCL_IO19 11 GND 12 I2S_DOUT_IO16 13 I2S_BCLK_IO7 14 GND 15 I2S_WS_IO8 16 I2S_DIN_IO17

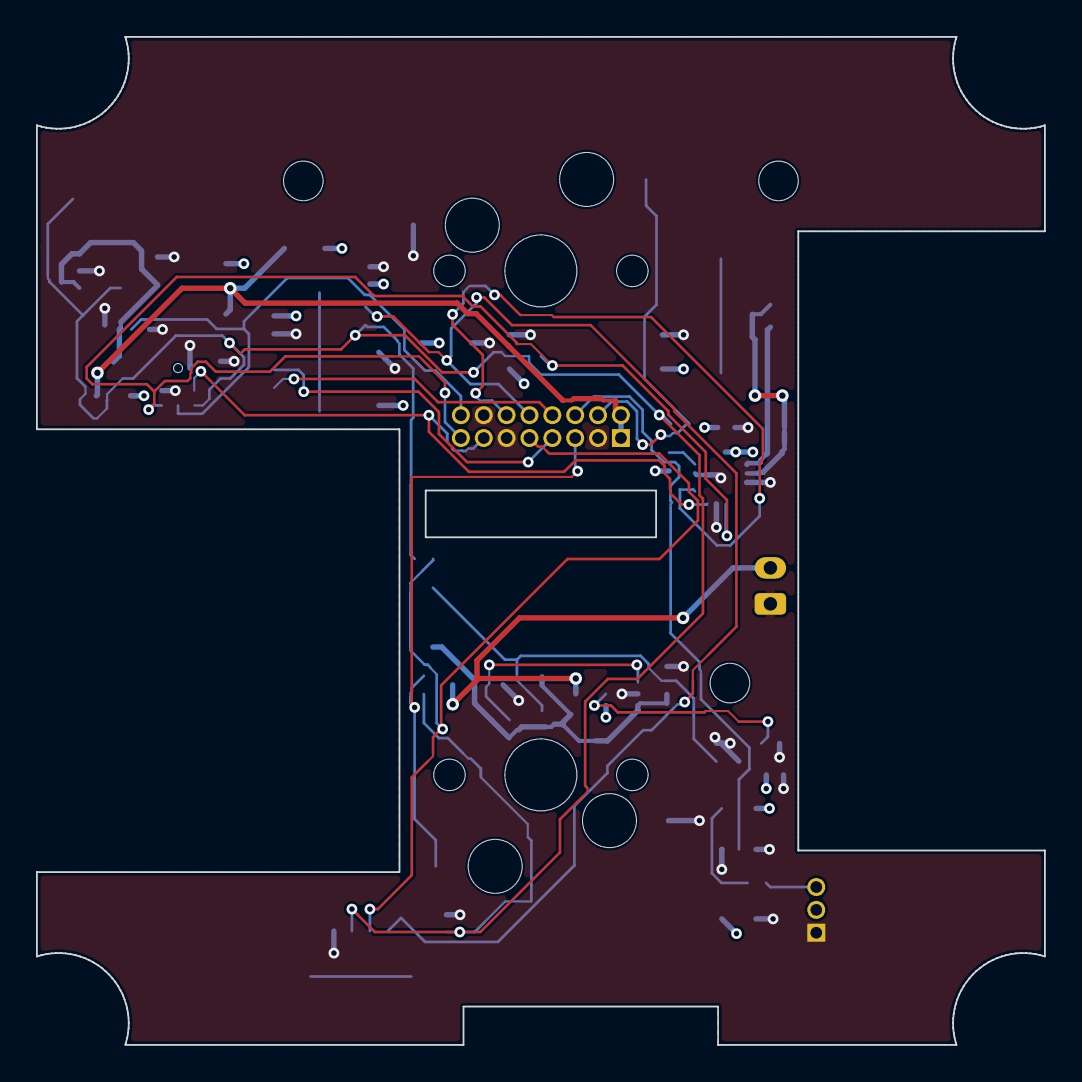
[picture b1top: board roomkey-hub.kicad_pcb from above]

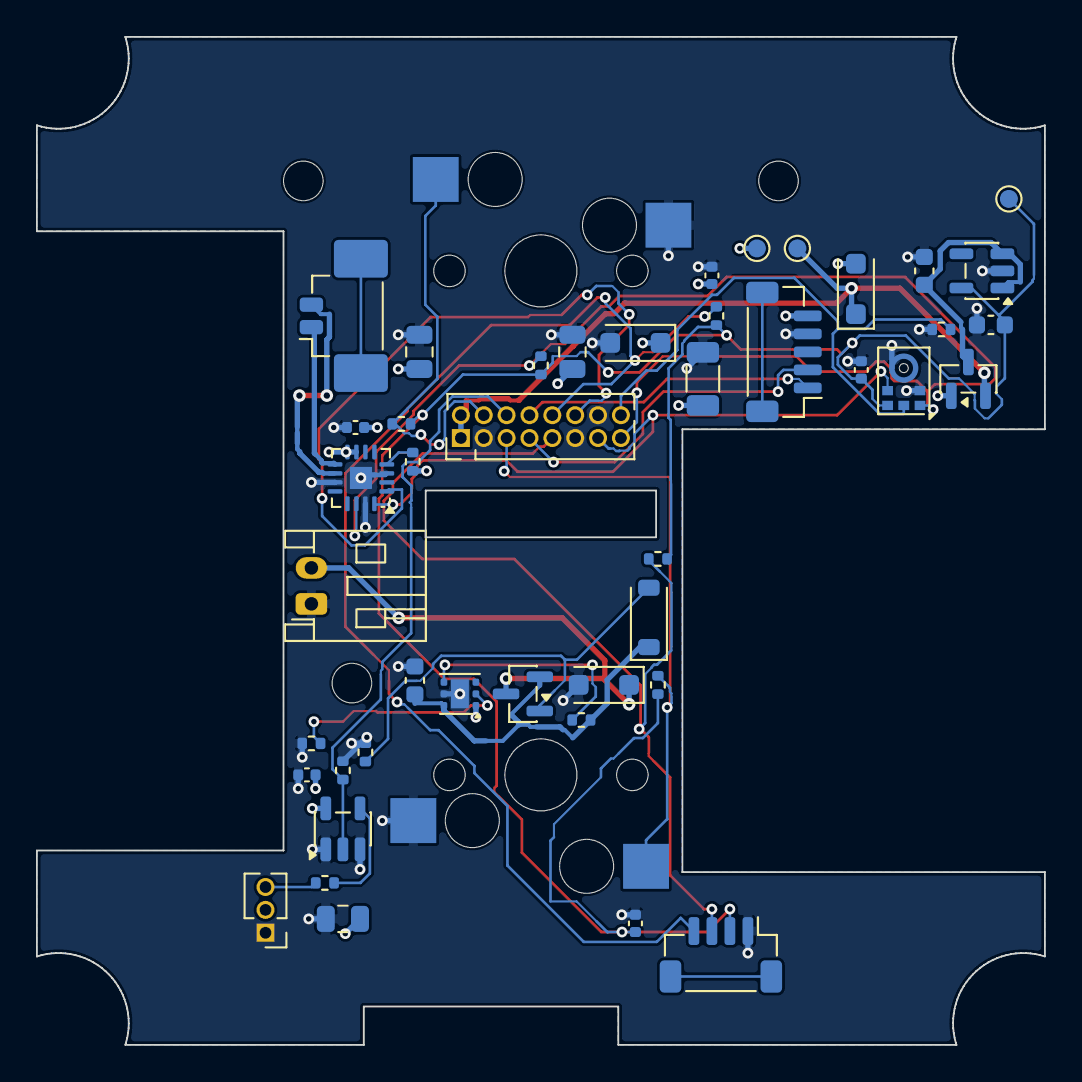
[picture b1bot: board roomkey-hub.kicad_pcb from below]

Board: 4 copper layers, 56.0 x 56.0 mm, 49 parts (49 on the bottom side), 26 nets.

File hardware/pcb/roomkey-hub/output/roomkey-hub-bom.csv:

"Reference","Value","MPN","Manufacturer","LCSC","Footprint","QUANTITY","DNP"
"C1,C5,C6","1u","CL10A105KB8NNNC","Samsung","C15849","Capacitor_SMD:C_0603_1608Metric","3",""
"C2","100u","CL31A107MQHNNNE","Samsung","C15008","Capacitor_SMD:C_1206_3216Metric","1",""
"C3,C7,C14","10u","CL21A106KAYNNNE","Samsung","C15850","Capacitor_SMD:C_0805_2012Metric","3",""
"C4,C8,C9,C13,C15","100n","CL05B104KO5NNNC","Samsung","C1525","Capacitor_SMD:C_0402_1005Metric","5",""
"D1","SMF12CA","SMF12CA","MDD","C123801","Diode_SMD:D_SOD-123F","1",""
"D2","BZT52C6V2","LBZT52C6V2T1G","LRC","C27091","Diode_SMD:D_SOD-123","1",""
"D3","SMF5.0A","SMF5.0A","MDD","C193402","Diode_SMD:D_SOD-123F","1",""
"D4","PMEG3020EH","PMEG3020EH","TECH PUBLIC","C19268151","Diode_SMD:D_SOD-123F","1",""
"D5","BAT54C","BAT54C","Changjiang (CJ)","C2135","Package_TO_SOT_SMD:SOT-23","1",""
"J1","5V IN","S2B-PH-K-S(LF)(SN)","JST","C173752","Connector_JST:JST_PH_S2B-PH-K_1x02_P2.00mm_Horizontal","1",""
"J2","SPEAKER","A1251WV-S-2P","CJT","C225104","Connector_Molex:Molex_PicoBlade_53398-0271_1x02-1MP_P1.25mm_Vertical","1",""
"J5","RADAR","BM05B-SRSS-TB(LF)(SN)","JST","C160391","Connector_JST:JST_SH_BM05B-SRSS-TB_1x05-1MP_P1.00mm_Vertical","1",""
"J9","SHT TAIL","BM04B-SRSS-TB(LF)(SN)","JST","C160390","Connector_JST:JST_SH_BM04B-SRSS-TB_1x04-1MP_P1.00mm_Vertical","1",""
"Q1","AO3401A","AO3401A","Alpha & Omega Semiconductor","C15127","Package_TO_SOT_SMD:SOT-23","1",""
"R1,R5,R15","100k","0402WGF1003TCE","UNI-ROYAL","C25741","Resistor_SMD:R_0402_1005Metric","3",""
"R2","64.9k","0402WGF6492TCE","UNI-ROYAL","C26984","Resistor_SMD:R_0402_1005Metric","1",""
"R3,R17","1M","0402WGF1004TCE","UNI-ROYAL","C26083","Resistor_SMD:R_0402_1005Metric","2",""
"R6,R13,R14","10k","0402WGF1002TCE","UNI-ROYAL","C25744","Resistor_SMD:R_0402_1005Metric","3",""
"R11,R12","4.7k","0402WGF4701TCE","UNI-ROYAL","C25900","Resistor_SMD:R_0402_1005Metric","2","DNP"
"R16","330","0402WGF3300TCE","UNI-ROYAL","C25104","Resistor_SMD:R_0402_1005Metric","1",""
"SW1","MX top","CPG151101S11-2","HanElectricity","C49352235","roomkey:SW_MX_Hotswap_Kailh_1.00u","1",""
"SW2","MX bottom","CPG151101S11-2","HanElectricity","C49352235","roomkey:SW_MX_Hotswap_Kailh_1.00u","1",""
"U1","TPS25200DRVR","TPS25200DRVR","Texas Instruments","C128401","Package_SON:WSON-6-1EP_2x2mm_P0.65mm_EP1x1.6mm","1",""
"U2","TPS7A2033PDBVR","TPS7A2033PDBVR","Texas Instruments","C2862740","Package_TO_SOT_SMD:SOT-23-5","1",""
"U3","MAX98357AETE+T","MAX98357AETE+T","Analog Devices","C910544","Package_DFN_QFN:TQFN-16-1EP_3x3mm_P0.5mm_EP1.23x1.23mm","1",""
"U4","ICS-43434","ICS-43434","TDK InvenSense","C5656610","Sensor_Audio:InvenSense_ICS-43434-6_3.5x2.65mm","1",""
"U7","SN74AHCT1G125DBVR","SN74AHCT1G125DBVR","Texas Instruments","C7484","Package_TO_SOT_SMD:SOT-23-5","1",""
